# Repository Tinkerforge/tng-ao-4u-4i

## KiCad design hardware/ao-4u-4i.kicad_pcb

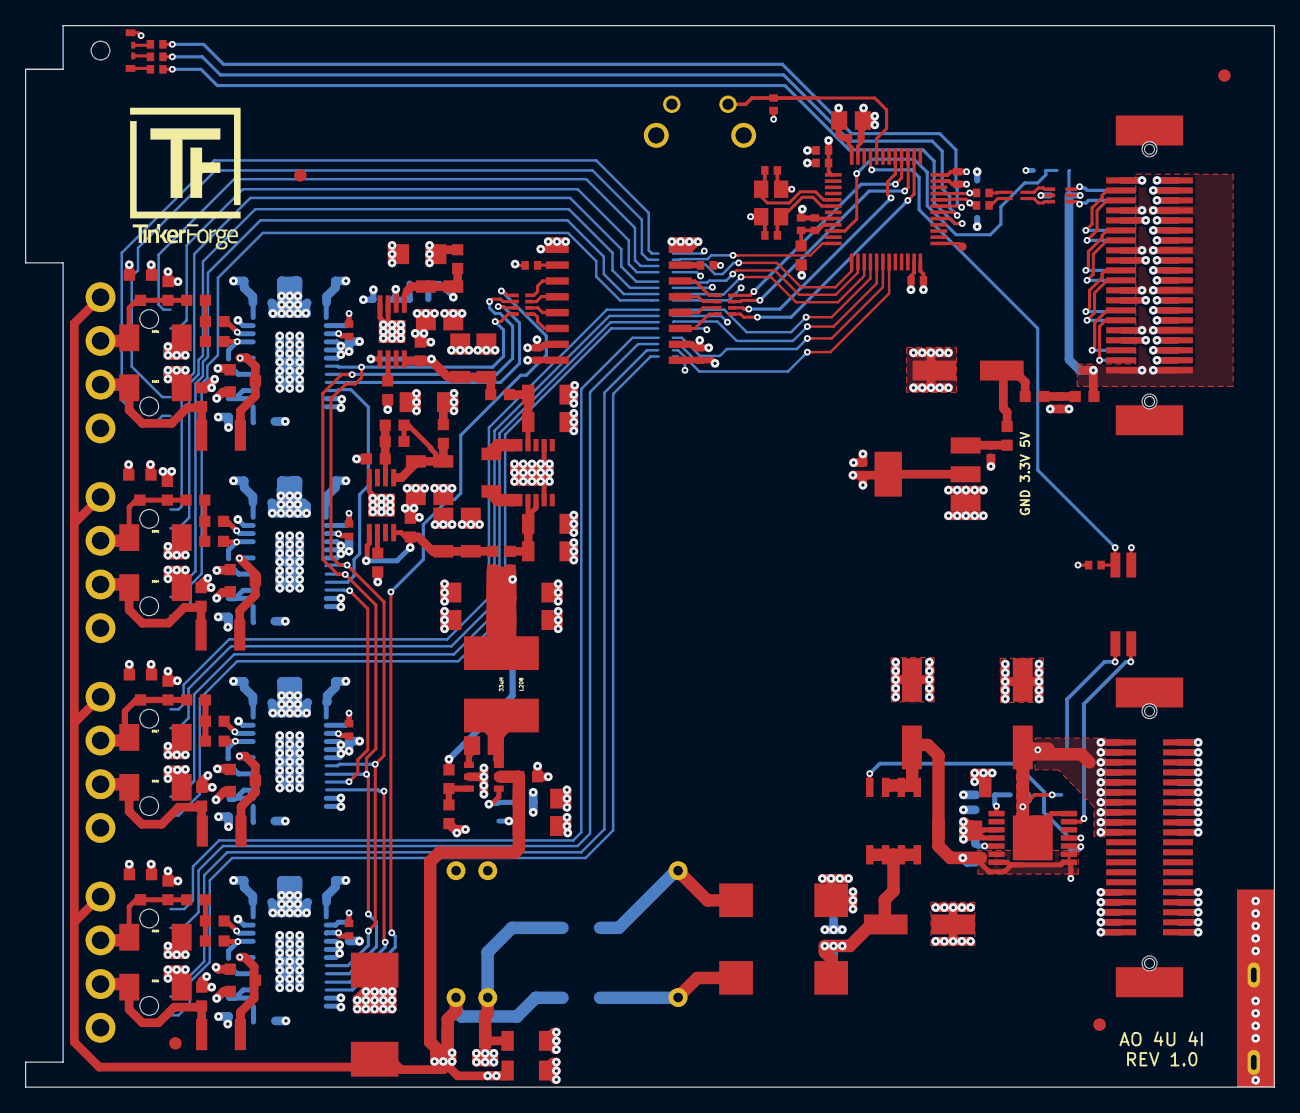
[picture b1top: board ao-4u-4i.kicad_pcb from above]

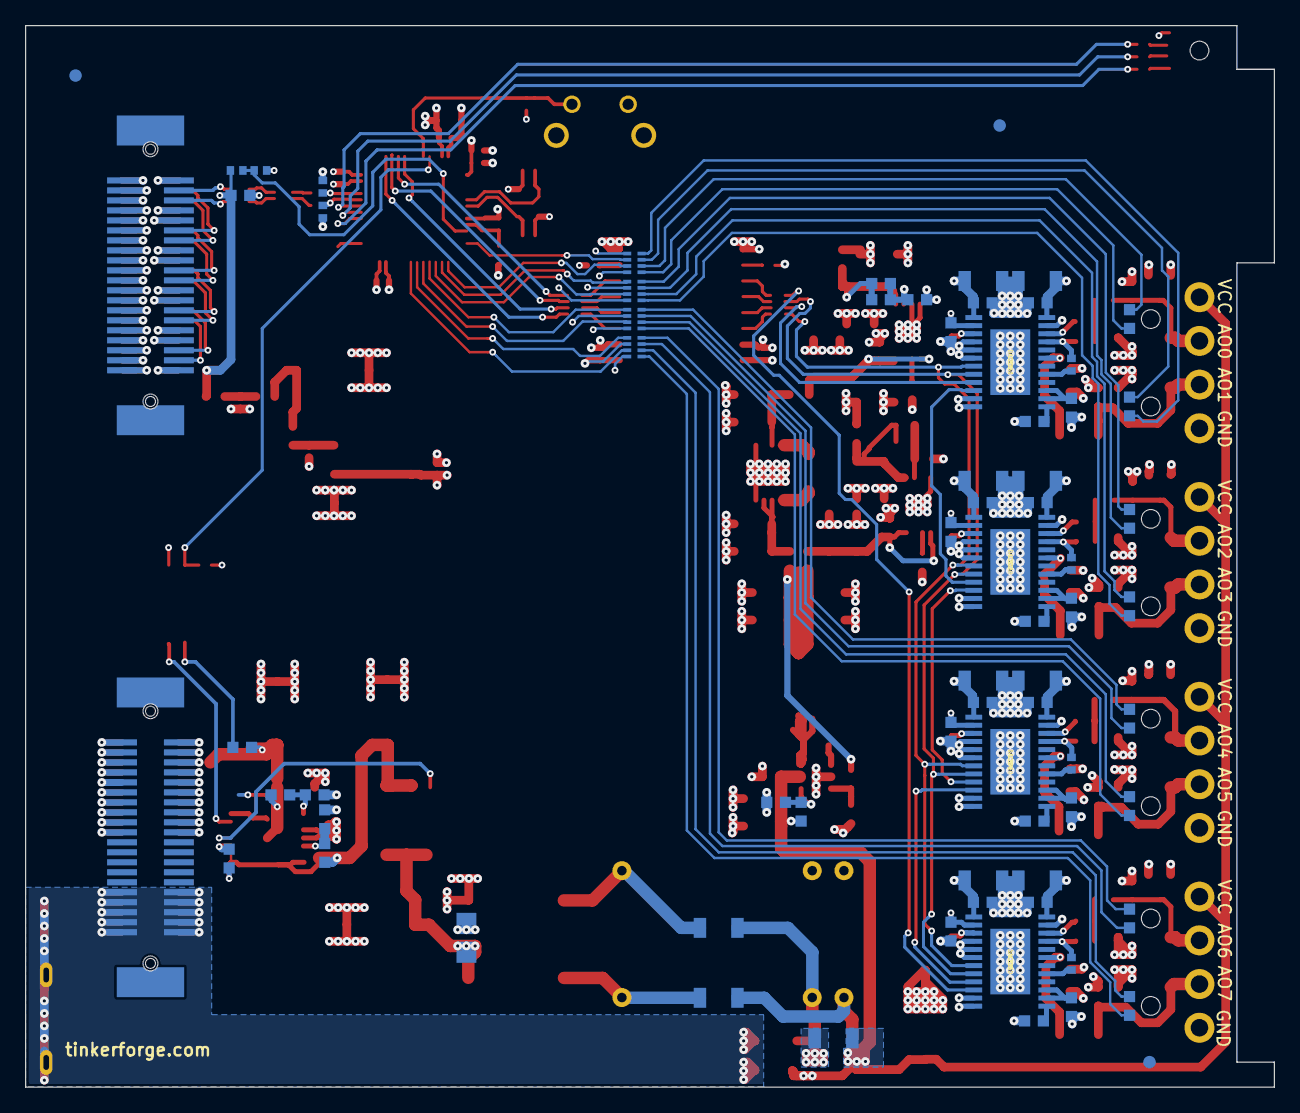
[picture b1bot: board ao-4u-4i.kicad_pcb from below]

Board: 4 copper layers, 100.0 x 85.0 mm, 224 parts (73 on the bottom side), 158 nets.

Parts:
C101, C102, C116, C117: 1uF; C0402F
C103, C104, C105, C106, C107, C112, C233, C235: 100nF; C0402F
C108, C109: 33pF; C0402F
C110: 10uF; C0805E
C111, C122, C123, C124: 100uF/35V; ELKO_63
C113, C114: 47pF; C0402F
C115: 2.2uF; C0603F
C118: 10uF/50V; C1206
C119, C120: 0; C1206
C121, C125, C126: 10uF/35V; C1206
C127, C128: 1nF/2kV; C1206
C201, C202, C203, C204, C207, C209, C211, C212, C213, C215, C217, C218, C219, C220, C221, C222, C225, C227, C229, C230, C231, C234, C237, C238, C245, C246, C258: 100nF/30V; C0603F
C205, C206, C223, C224: 1nF; C0402F
C208, C210, C214, C216, C226, C228, C232, C236, C239, C242: 4.7uF/30V; C1206
C240, C241, C243, C244, C247, C251, C252, C255, C257, C259, C260, C261, C262, C263, C264, C265, C266, C267: 4.7uF/50V; C1206
C248, C249, C253, C254: 10nF/30V; C0603F
C250: 100nF/100V; C0805E
C256: 1uF/50V; C1206
D101: 3.0SMI30CATR; SMC
D201, D202, D213, D214, D217, D218, D221, D222: SMBJ18CA; SMB
D203, D204, D205, D206, D207, D208, D209, D210: LED; LED-LP
D211, D212, D215, D216, D219, D220, D223, D224: CDSOT23-T15C; SOT23-3
Fiducial_Mark: VAL**; Fiducial_Mark
Fiducial_Mark#2, Fiducial_Mark#3, Fiducial_Mark#4, Fiducial_Mark#5, Fiducial_Mark#6, Fiducial_Mark#7: VAL**; Fiducial_Mark
J101: TNG-Power-TOP; TNG-40-TOP
J102: TNG-Power-BTM; TNG-40-BTM
J103: TNG-Data-TOP; TNG-40-TOP
J104: TNG-Data-BTM; TNG-40-BTM
L101: FB; R0603F
L102, L103, L104: INDUCTs; R0603F
L105: 744230900; WE-CNSW-0603
L201, L202, L203, L204, L205, L206, L207, L209, L210: FB; C0603F
L208: 33uH; SRN6045
LED101: EASV3015RGBA0; LED-RGB-LP
P102: Debug; DEBUG_PAD
P103: PE; PE_Hook
P201: OUTPUT0; OQ_4P
P202: OUTPUT1; OQ_4P
P203: OUTPUT2; OQ_4P
P204: OUTPUT3; OQ_4P
Q101: FDS8449; SOIC-8-MOSFET
R101, R107, R108: 1k; R0402F
R102, R105, R221, R254: 0; R0402F
R103, R104: 22; R0402F
R106: 56; R0402F
R109, R209, R210, R219, R220: 10k; R0402F
R110, R115: 10k; R0603F
R111, R112: DNP; R0603F
R113: 22; R0603F
R114: 68k; R0603F
R116: VC1206K201R030; R1206
R201, R202, R204, R205, R211, R212, R214, R215: 15; R0603F
R203, R206, R213, R216: 15 1/2W 1%; R1210
R207, R208, R217, R218: 15k 0.1%; R0603F
R222: 127k; R0603F
R223: 1.37M; R0603F
R224, R227: 110k; R0603F
R225, R226: 9.42k; R0603F
R228: 374k; R0603F
R229: 22.1k; R0603F
RP201, RP202, RP203, RP204, RP205, RP206: 470; 4X0402
SW101: BOOT; TACT-6MM-HOR
T101: 744273222; WE-SL5
U101: STM32F070CBT6; LQFP48
U102: AZ1117EH; SOT-223
U103: 82400152; SOT563-SPEC
U104: DNP; TEL10
U105: TLP293; SOP4
U106: STEF01; HTSSOP14
U201, U202, U204, U205: DAC8760; TSSOP24-44-PWR
U203: ISO7741DWR; SOIC16_WIDE
U206: TPS560430YDBVR; SOT23-6
U207: TPS7A3001DGNR; MSOP-8-EP
U208: TPS7A4901DGNR; MSOP-8-EP
U209: LTC3261; MSOP12_EXP
X101: 8MHz; CRYSTAL_3225

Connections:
3V3: C101.1, C103.1, C104.1, C105.1, C106.1, C110.1, C116.1, C235.1, L101.1, LED101.1, R109.2, R254.1, RP201.1, RP201.4, RP202.2, RP202.4, RP203.2, RP203.4, RP204.2, RP204.4, SW101.1, U101.1, U101.24, U101.36, U101.48, U102.2, U203.1
5VA: C115.1, J103.7, J103.8, J103.15, J103.16, J103.23, J103.24, J103.31, J103.32, J103.39, J103.40, J104.7, J104.8, J104.15, J104.16, J104.23, J104.24, J104.31, J104.32, J104.39, J104.40, L104.1, R107.1, U103.5
+5V: C111.1, L102.1, L103.2
+15V: C207.2, C208.2, C209.2, C210.2, C225.2, C226.2, C227.2, C228.2, C240.2, D211.2, D212.2, D215.2, D216.2, D219.2, D220.2, D223.2, D224.2, L206.2, U201.24, U202.24, U204.24, U205.24
-15V: C213.1, C214.1, C215.1, C216.1, C231.1, C232.1, C234.1, C236.1, C265.2, D211.1, D212.1, D215.1, D216.1, D219.1, D220.1, D223.1, D224.1, L209.2, U201.1, U201.EP, U202.1, U202.EP, U204.1, U204.EP, U205.1, U205.EP
AGND: C118.2, C120.1, C128.2, C201.1, C202.1, C203.1, C204.1, C207.1, C208.1, C209.1, C210.1, C211.1, C212.1, C213.2, C214.2, C215.2, C216.2, C217.1, C218.1, C219.1, C220.1, C221.1, C222.1, C225.1, C226.1, C227.1, C228.1, C229.1, C230.1, C231.2, C232.2, C233.2, C234.2, C236.2, C237.1, C238.1, C239.1, C240.1, C241.1, C242.1, C243.1, C244.1, C245.1, C246.2, C247.1, C248.1, C251.1, C252.1, C254.1, C255.1, C257.1, C258.2, C259.1, C260.1, C261.1, C262.1, C263.1, C264.1, C265.1, C266.1, C267.1, D101.2, D201.1, D202.1, D213.1, D214.1, D217.1, D218.1, D221.1, D222.1, P201.4, P202.4, P203.4, P204.4, R116.2, R207.2, R208.2, R217.2, R218.2, R222.2, R225.1, R226.1, R229.1, U104.10, U201.4, U201.5, U201.6, U201.11, U201.12, U201.23, U202.4, U202.5, U202.6, U202.11, U202.12, U202.23, U203.9, U203.15, U204.4, U204.5, U204.6, U204.11, U204.12, U204.23, U205.4, U205.5, U205.6, U205.11, U205.12, U205.23, U206.2, U207.3, U207.4, U207.EP, U208.4, U208.EP, U209.2, U209.11, U209.EXP
AGNDA: C121.2, C122.2, C123.2, C124.2, C125.2, C126.2, J101.2, J101.4, J101.6, J101.8, J101.10, J101.12, J101.14, J101.16, J101.18, J101.20, J102.1, J102.3, J102.5, J102.7, J102.9, J102.11, J102.13, J102.15, J102.17, J102.19, R112.2, R115.2, T101.2, U106.3, U106.4
AIN0: R107.2, R108.1, U101.10
DVDD: C217.2, C233.1, R209.2, R221.2, U201.2, U203.16
Earth: C127.2, C128.1, J101.31, J101.32, J101.33, J101.34, J101.35, J101.36, J101.37, J101.38, J101.39, J101.40, J102.31, J102.32, J102.33, J102.34, J102.35, J102.36, J102.37, J102.38, J102.39, J102.40, P103.1
GND: C101.2, C102.2, C103.2, C104.2, C105.2, C106.2, C107.2, C108.1, C109.1, C110.2, C111.2, C112.2, C113.2, C114.2, C115.2, C116.2, C117.2, C235.2, J103.1, J103.2, J103.4, J103.6, J103.9, J103.10, J103.12, J103.14, J103.17, J103.18, J103.20, J103.22, J103.25, J103.26, J103.28, J103.30, J103.33, J103.34, J103.36, J103.38, J104.1, J104.2, J104.3, J104.5, J104.9, J104.10, J104.11, J104.13, J104.17, J104.18, J104.19, J104.21, J104.25, J104.26, J104.27, J104.29, J104.33, J104.34, J104.35, J104.37, R101.1, R108.2, U101.8, U101.23, U101.35, U101.47, U102.1, U103.2, U105.3, U203.2, U203.8, X101.3
LED0: RP201.2, U101.12
LED1: RP201.3, U101.13
LED2: RP202.1, U101.14
LED3: RP202.3, U101.15
LED4: RP203.1, U101.16
LED5: RP203.3, U101.17
LED6: RP204.1, U101.18
LED7: RP204.3, U101.19
LEDB: R106.1, U101.31
LEDG: R105.1, U101.30
LEDR: R102.1, U101.29
unnamed: C102.1, C107.1, L101.2, U101.9
unnamed: C108.2, U101.5, X101.2
unnamed: C109.2, U101.6, X101.1
unnamed: C112.1, L103.1, L104.2
unnamed: C117.1, L102.2, U102.3
unnamed: C119.2, T101.4, U104.16
unnamed: C120.2, T101.3, U104.1
unnamed: C121.1, C123.1, Q101.D, T101.1
unnamed: C201.2, D201.2, D211.3, L201.2, P201.2
unnamed: C202.2, D202.2, D212.3, L203.2, P202.2
unnamed: C203.2, D213.2, P201.3, R203.1
unnamed: C204.2, D214.2, P202.3, R206.1
unnamed: C205.1, U201.17
unnamed: C205.2, R202.2, U201.21
unnamed: C206.1, U202.17
unnamed: C206.2, R205.2, U202.21
unnamed: C211.2, U201.14, U201.15
unnamed: C212.2, U202.14, U202.15
unnamed: C218.2, R210.2, U202.2
unnamed: C219.2, D217.2, D219.3, L204.2, P203.2
unnamed: C220.2, D218.2, D220.3, L205.2, P204.2
unnamed: C221.2, D221.2, P203.3, R213.1
unnamed: C222.2, D222.2, P204.3, R216.1
unnamed: C223.1, U204.17
unnamed: C223.2, R212.2, U204.21
unnamed: C224.1, U205.17
unnamed: C224.2, R215.2, U205.21
unnamed: C229.2, U204.14, U204.15
unnamed: C230.2, U205.14, U205.15
unnamed: C237.2, R219.2, U204.2
unnamed: C238.2, R220.2, U205.2
unnamed: C241.2, C243.2, C246.1, L207.1, U207.5, U207.8
unnamed: C244.2, C247.2, C249.1, L206.1, R224.2, U208.1
unnamed: C248.2, U207.6
unnamed: C249.2, R224.1, R225.2, U208.2
unnamed: C250.1, L208.1, U206.6
unnamed: C250.2, U206.1
unnamed: C251.2, C252.2, L207.2, U209.4
unnamed: C253.1, C257.2, C260.2, L209.1, R227.2, U207.1
unnamed: C253.2, R226.2, R227.1, U207.2
unnamed: C254.2, U208.6
unnamed: C255.2, C259.2, C262.2, C267.2, L202.2, L208.2, L210.2, R228.2
unnamed: C256.1, U209.5, U209.6
unnamed: C256.2, U209.7, U209.8
unnamed: C258.1, C261.2, C264.2, L202.1, U208.5, U208.8
unnamed: C263.2, C266.2, L210.1, U209.9, U209.10
unnamed: D203.1, RP201.5
unnamed: D203.2, RP201.6
unnamed: D204.1, RP201.8
unnamed: D204.2, RP201.7
unnamed: D205.1, RP202.7
unnamed: D205.2, RP202.8
unnamed: D206.1, RP202.5
unnamed: D206.2, RP202.6
unnamed: D207.1, RP203.7
unnamed: D207.2, RP203.8
unnamed: D208.1, RP203.5
unnamed: D208.2, RP203.6
unnamed: D209.1, RP204.7
unnamed: D209.2, RP204.8
unnamed: D210.1, RP204.5
unnamed: D210.2, RP204.6
unnamed: D215.3, R203.2, U201.19
unnamed: D216.3, R206.2, U202.19
unnamed: D223.3, R213.2, U204.19
unnamed: D224.3, R216.2, U205.19
unnamed: J103.3, J104.12
unnamed: J103.5, J104.14
unnamed: J103.11, J104.20
unnamed: J103.13, J104.22
unnamed: J103.19, J104.28
unnamed: J103.21, J104.30
unnamed: J103.27, J104.36
unnamed: J103.29, J104.38
unnamed: L201.1, R201.1, R202.1
unnamed: L203.1, R204.1, R205.1
unnamed: L204.1, R211.1, R212.1
unnamed: L205.1, R214.1, R215.1
unnamed: LED101.2, R106.2
unnamed: LED101.3, R105.2
unnamed: LED101.4, R102.2
unnamed: P102.1, U101.25
unnamed: Q101.G, U106.11
unnamed: R101.2, SW101.2, U101.44
unnamed: R110.2, U105.1
unnamed: R111.2, R112.1, U106.5
unnamed: R113.2, U106.10
unnamed: R114.2, R115.1, U106.1
unnamed: R201.2, U201.22
unnamed: R204.2, U202.22
unnamed: R207.1, U201.13
unnamed: R208.1, U202.13
unnamed: R209.1, U201.3
unnamed: R210.1, U202.3
unnamed: R211.2, U204.22
unnamed: R214.2, U205.22
unnamed: R217.1, U204.13
unnamed: R218.1, U205.13
unnamed: R219.1, U204.3
unnamed: R220.1, U205.3
unnamed: R221.1, U203.10
unnamed: R222.1, R223.1, U206.4
unnamed: R228.1, R229.2, U206.3
unnamed: R254.2, U203.7
unnamed: RP205.1, U203.14
unnamed: RP205.2, U203.13
unnamed: RP205.3, U203.12
unnamed: RP205.4, U203.11
unnamed: RP206.5, U203.6
unnamed: RP206.6, U203.5
unnamed: RP206.7, U203.4
unnamed: RP206.8, U203.3
unnamed: U201.10, U202.9
unnamed: U202.10, U204.9
unnamed: U204.10, U205.9
PWR_GOOD: R109.1, U101.45, U105.4
PWR_PG: U105.2, U106.13
SPI-CLK: RP206.3, U101.39
SPI-LATCH: RP206.1, U101.38
SPI-MISO: RP206.4, U101.40
SPI-MOSI: RP206.2, U101.41
USB-DM: C114.1, R104.2, U101.32
USB-DMA: J104.6, U103.4
USB-DMB: L105.1, U103.3
USB-DMC: L105.2, R104.1
USB-DP: C113.1, R103.2, U101.33
USB-DPA: J104.4, U103.6
USB-DPB: L105.4, U103.1
USB-DPC: L105.3, R103.1
VCC: C118.1, C119.1, C127.1, C239.2, C242.2, C245.2, D101.1, P201.1, P202.1, P203.1, P204.1, R116.1, R223.2, U104.9, U206.5
VCCPWRA: C122.1, C126.1, J101.1, J101.3, J101.5, J101.7, J101.9, J101.11, J101.13, J101.15, J101.17, J101.19, J102.2, J102.4, J102.6, J102.8, J102.10, J102.12, J102.14, J102.16, J102.18, J102.20, R110.1, R114.1, U106.14, U106.EXP
VO: C124.1, C125.1, Q101.S, R111.1, R113.1, U106.6, U106.7, U106.8, U106.9
_SPI-CLK: RP205.6, U201.8, U202.8, U204.8, U205.8
_SPI-LATCH: RP205.8, U201.7, U202.7, U204.7, U205.7
_SPI-MISO: RP205.5, U205.10
_SPI-MOSI: RP205.7, U201.9

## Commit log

2020-01-02 start with schematic
2020-01-03 footprint draft finished
2020-01-03 placement draft
2020-01-06 placement complete
2020-01-06 some routing
2020-01-20 more routing
2020-03-02 fix footprint spacing, fix description
2020-03-02 add hook footprint
2020-03-17 change esd diodes
2020-05-14 fix values
2020-05-14 specify value
2020-07-02 fix diode values
2020-07-03 fix isolator enable resistors
2020-07-03 fix diodes
2020-07-20 Add initial firmware
    with
    * DAC8760 driver and
    * initial simplified API
2020-07-20 Add .gitinore
2020-07-27 Use HAL Config from bricklib2
2020-07-27 Add TIM defines for status LEDs
2020-09-04 add version 1,1
    fix footprints
2020-09-04 fix text layer
2020-09-04 fix tbd
2020-09-04 fix diode orientation
2020-09-07 specify capacitors
2020-09-07 fix stuff
2020-09-07 improve routing
2020-09-08 all footprints updated
2020-09-09 remove galvanic isolation as default
2020-09-10 fix 3d stuff

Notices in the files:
hardware/ao-4u-4i.kicad_pcb:
Licensed under CERN OHL v.1.1
Copyright (©) 2020, B.Nordmeyer
Copyright Tinkerforge GmbH 2020.
This documentation describes Open Hardware and is licensed under the
CERN OHL v. 1.1.
